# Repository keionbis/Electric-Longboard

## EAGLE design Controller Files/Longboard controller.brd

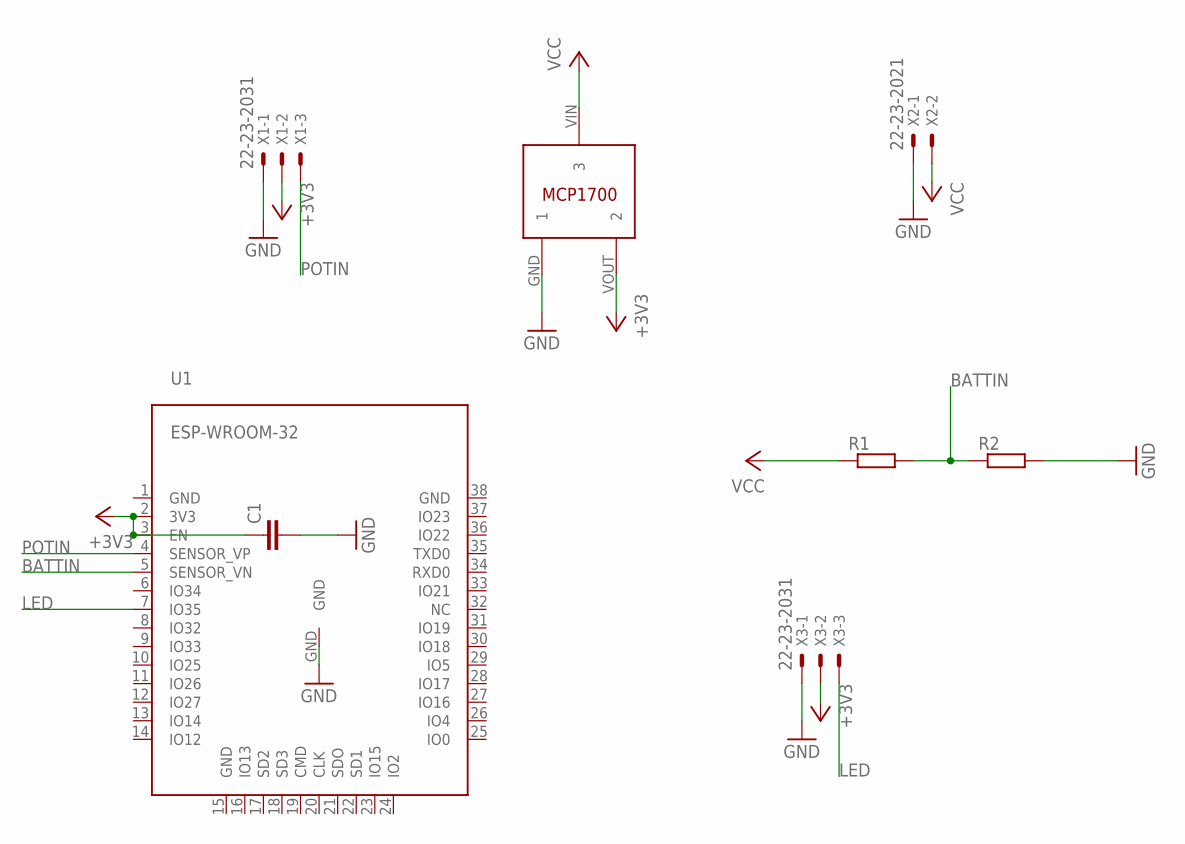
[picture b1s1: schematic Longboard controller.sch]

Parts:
C1: C-EUC0402; C0402
R1, R2: R-EU_R0805; R0805
U1: ESP-WROOM-32
U$1: MCP1700T-3302E/TT
X1, X3: 22-23-2031
X2: 22-23-2021

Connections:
+3V3: C1.1, U1.2 (3V3), U1.3 (EN), U$1.VOUT (2), X1.2, X3.2
BATTIN: R1.2, R2.1, U1.5 (SENSOR_VN)
GND: C1.2, R2.2, U1.GND, U$1.GND (1), X1.1, X2.1, X3.1
LED: U1.7 (IO35), X3.3
POTIN: U1.4 (SENSOR_VP), X1.3
VCC: R1.1, U$1.VIN (3), X2.2

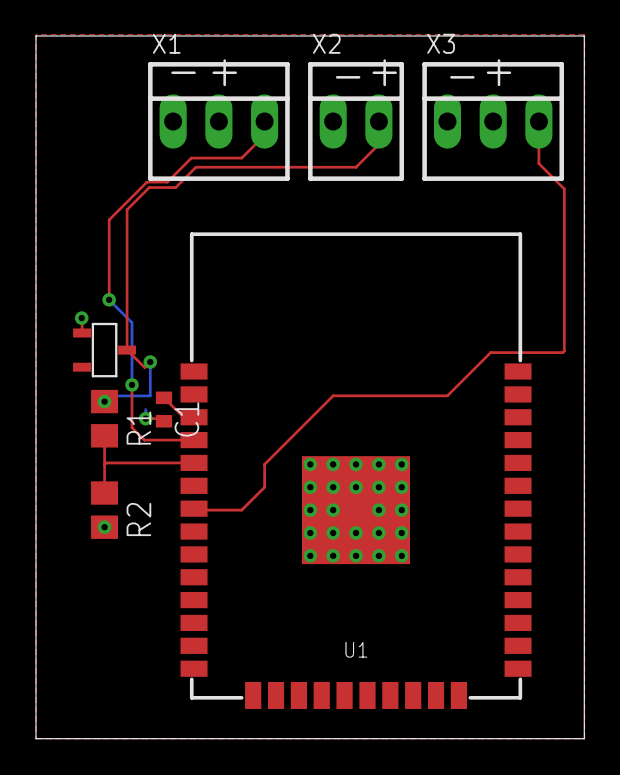
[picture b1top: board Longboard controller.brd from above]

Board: 2 copper layers, 30.5 x 39.0 mm, 8 parts (0 on the bottom side), 6 nets.

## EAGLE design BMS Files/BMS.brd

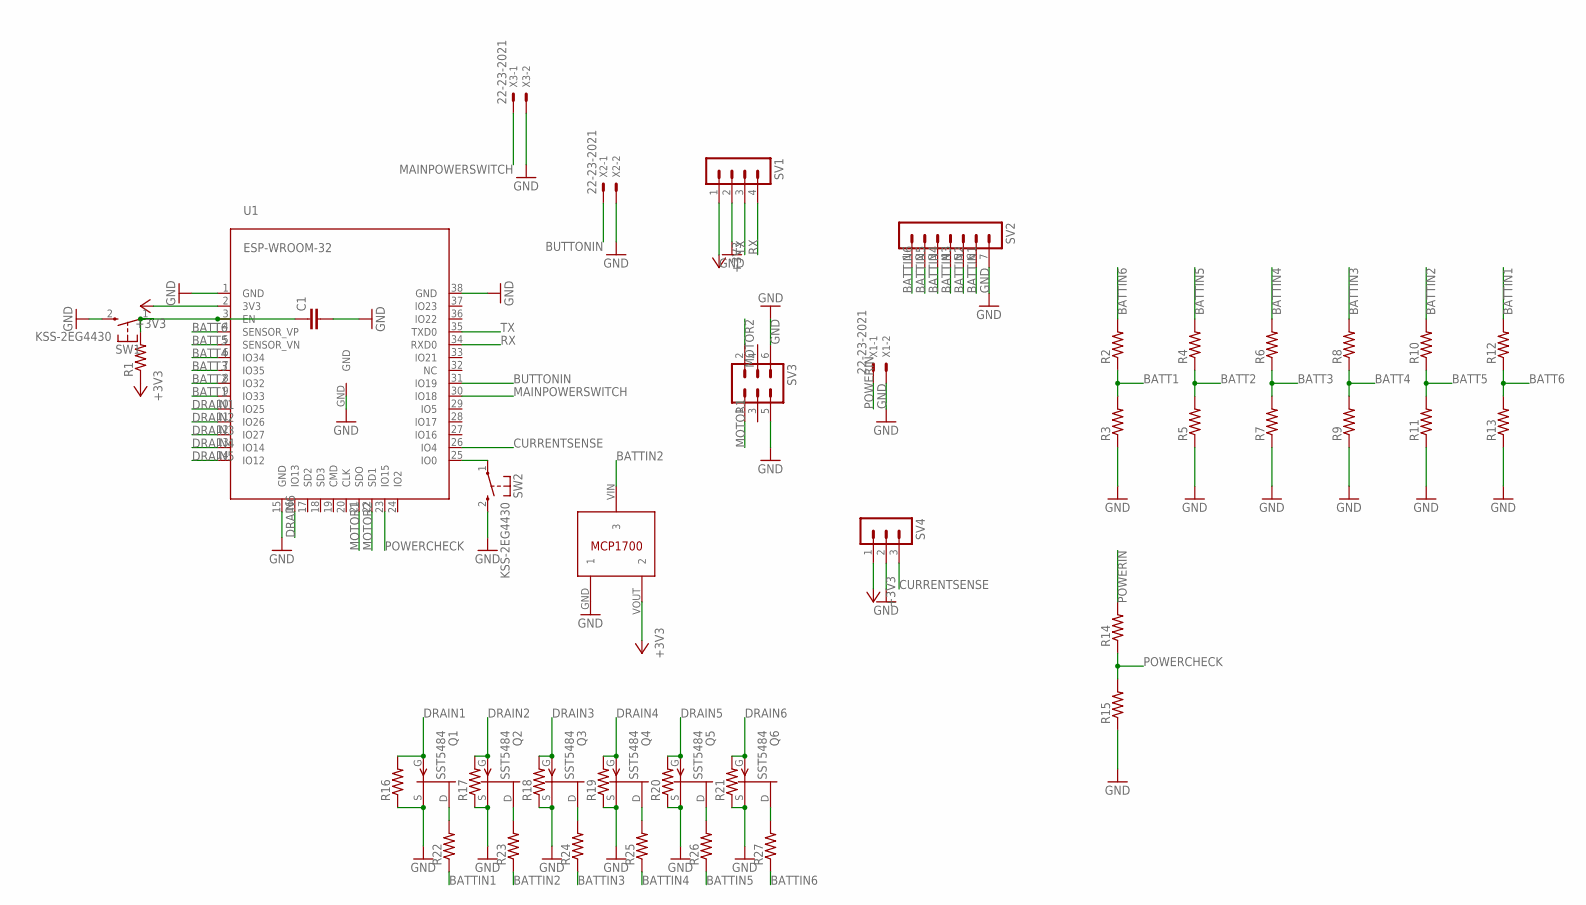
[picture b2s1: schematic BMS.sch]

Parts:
C1: C-EUC0402; C0402
Q1, Q2, Q3, Q4, Q5, Q6: SST5484; SOT23
R1: R-US_R0805; R0805
R2, R3, R4, R5, R6, R7, R8, R9, R10, R11, R12, R13, R14, R15, R16, R17, R18, R19, R20, R21, R22, R23, R24, R25, R26, R27: R-US_M0805; M0805
SV1: MA04-1
SV2: MA07-1
SV3: MA03-2
SV4: MA03-1
SW1, SW2: KSS-2EG4430
U1: ESP-WROOM-32
U$1: MCP1700T-3302E/TT
X1, X2, X3: 22-23-2021

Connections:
+3V3: R1.1, SV1.1, SV4.1, U1.2 (3V3), U$1.VOUT (2)
BATT1: R2.1, R3.2, U1.9 (IO33)
BATT2: R4.1, R5.2, U1.8 (IO32)
BATT3: R6.1, R7.2, U1.7 (IO35)
BATT4: R8.1, R9.2, U1.6 (IO34)
BATT5: R10.1, R11.2, U1.5 (SENSOR_VN)
BATT6: R12.1, R13.2, U1.4 (SENSOR_VP)
BATTIN1: R12.2, R22.1, SV2.6
BATTIN2: R10.2, R23.1, SV2.5, U$1.VIN (3)
BATTIN3: R8.2, R24.1, SV2.4
BATTIN4: R6.2, R25.1, SV2.3
BATTIN5: R4.2, R26.1, SV2.2
BATTIN6: R2.2, R27.1, SV2.1
BUTTONIN: U1.31 (IO19), X2.1
CURRENTSENSE: SV4.3, U1.26 (IO4)
DRAIN1: Q1.3 (G), R16.2, U1.10 (IO25)
DRAIN2: Q2.3 (G), R17.2, U1.11 (IO26)
DRAIN3: Q3.3 (G), R18.2, U1.12 (IO27)
DRAIN4: Q4.3 (G), R19.2, U1.13 (IO14)
DRAIN5: Q5.3 (G), R20.2, U1.14 (IO12)
DRAIN6: Q6.3 (G), R21.2, U1.16 (IO13)
GND: C1.2, Q1.2 (S), Q2.2 (S), Q3.2 (S), Q4.2 (S), Q5.2 (S), Q6.2 (S), R3.1, R5.1, R7.1, R9.1, R11.1, R13.1, R15.1, R16.1, R17.1, R18.1, R19.1, R20.1, R21.1, SV1.2, SV2.7, SV3.5, SV3.6, SV4.2, SW1.2 (S), SW2.2 (S), U1.1 (GND), U1.15 (GND), U1.38 (GND), U1.GND, U$1.GND (1), X1.2, X2.2, X3.2
MAINPOWERSWITCH: U1.30 (IO18), X3.1
MOTOR1: SV3.1, U1.21 (SDO)
MOTOR2: SV3.2, U1.22 (SD1)
unnamed: C1.1, R1.2, SW1.1, U1.3 (EN)
unnamed: SW2.1, U1.25 (IO0)
unnamed: Q6.1 (D), R27.2
unnamed: Q5.1 (D), R26.2
unnamed: Q4.1 (D), R25.2
unnamed: Q3.1 (D), R24.2
unnamed: Q2.1 (D), R23.2
unnamed: Q1.1 (D), R22.2
POWERCHECK: R14.1, R15.2, U1.23 (IO15)
POWERIN: R14.2, X1.1
RX: SV1.4, U1.34 (RXD0)
TX: SV1.3, U1.35 (TXD0)

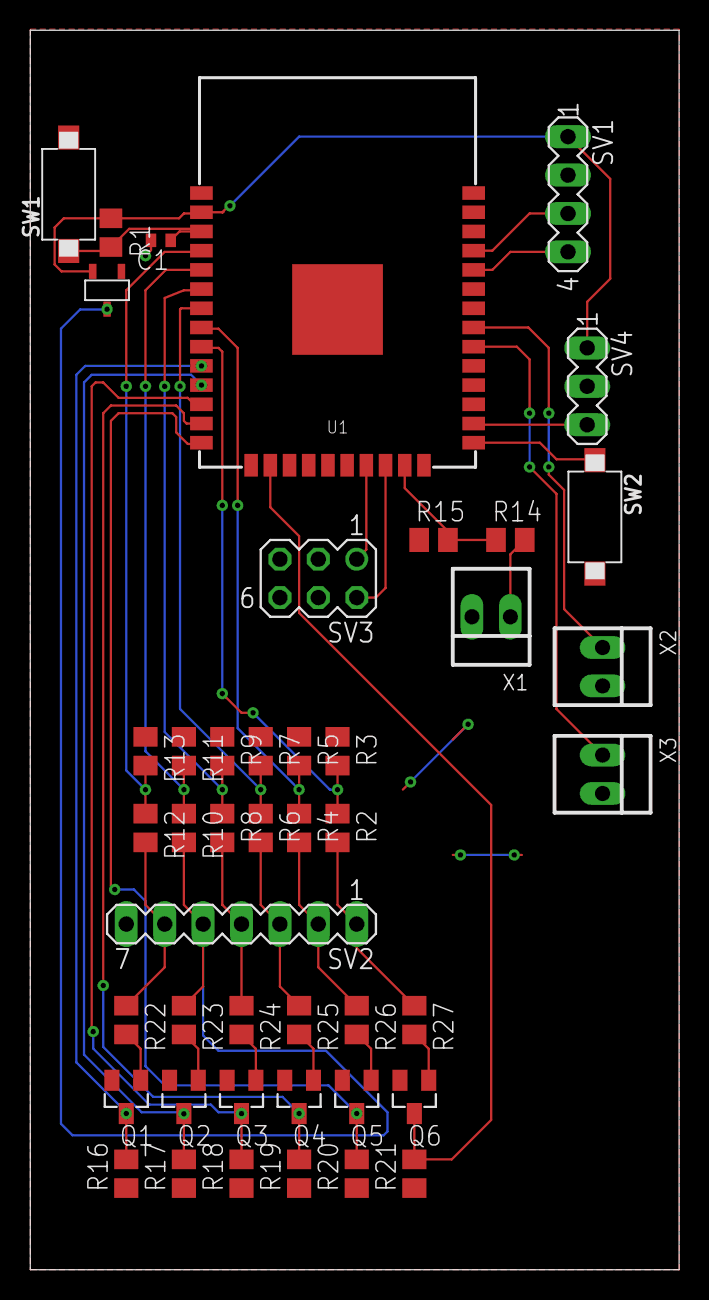
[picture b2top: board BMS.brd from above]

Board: 2 copper layers, 42.9 x 82.0 mm, 45 parts (0 on the bottom side), 37 nets.

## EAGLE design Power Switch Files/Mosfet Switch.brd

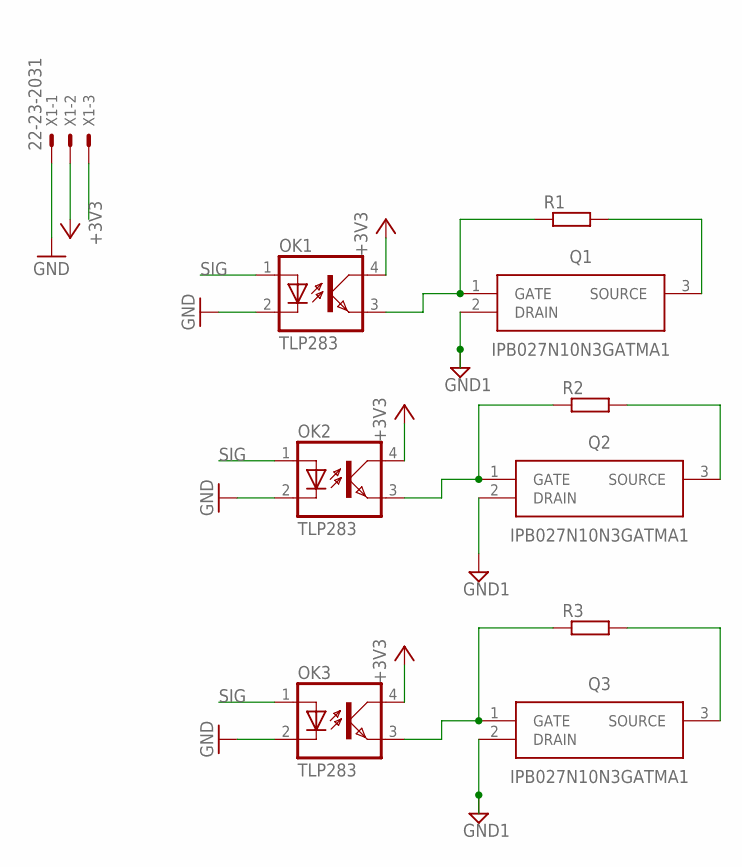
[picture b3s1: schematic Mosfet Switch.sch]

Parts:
OK1, OK2, OK3: TLP283; MINI-FLAT-4
Q1, Q2, Q3: IPB027N10N3GATMA1; PGTO263-3
R1, R2, R3: R-EU_R0805; R0805
X1: 22-23-2031

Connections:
+3V3: OK1.4 (COL), OK2.4 (COL), OK3.4 (COL), X1.2
GND1: Q1.2 (DRAIN), Q2.2 (DRAIN), Q3.2 (DRAIN)
GND2: OK1.2 (C), OK2.2 (C), OK3.2 (C), Q1.3 (SOURCE), Q2.3 (SOURCE), Q3.3 (SOURCE), R1.2, R2.2, R3.2, X1.1
unnamed: OK1.3 (EMIT), Q1.1 (GATE), R1.1
unnamed: OK2.3 (EMIT), Q2.1 (GATE), R2.1
unnamed: OK3.3 (EMIT), Q3.1 (GATE), R3.1
SIG: OK1.1 (A), OK2.1 (A), OK3.1 (A), X1.3

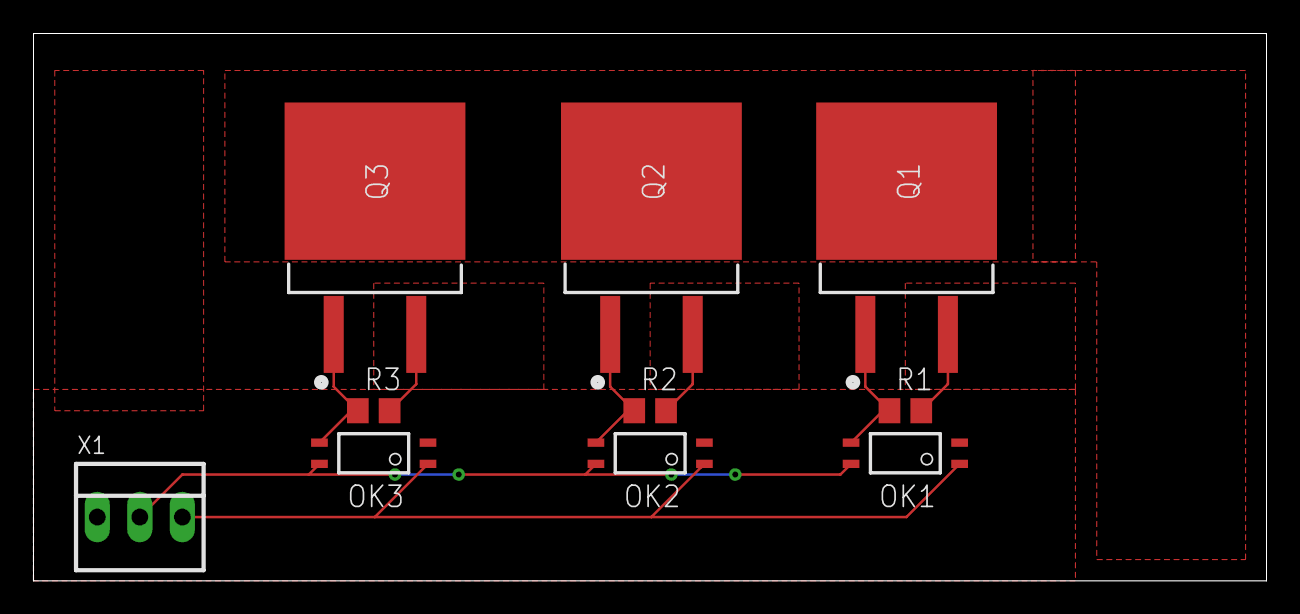
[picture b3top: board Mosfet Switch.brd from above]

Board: 2 copper layers, 73.6 x 32.7 mm, 10 parts (0 on the bottom side), 7 nets.

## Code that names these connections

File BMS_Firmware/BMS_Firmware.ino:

#include <esp_now.h>
#include <WiFi.h>
#include "esp32-hal-ledc.h"
#define CHANNEL 1
#define COUNT_LOW 0
#define COUNT_HIGH 1023
#define TIMER_WIDTH 10

#define PowerCheck 15
#define Drain1 25
#define Drain2 26
#define Drain3 27
#define Drain4 14
#define Drain5 12
#define Drain6 13
#define Batt6 36 
#define Batt5 39
#define Batt4 34
#define Batt3 35
#define Batt2 32
#define Batt1 33
#define currentSense 4

int State = 0;  //0 = driving State  1 = Charging State   2 =   

// Init ESP Now with fallback
void InitESPNow() {
  if (esp_now_init() == ESP_OK) {
    Serial.println("ESPNow Init Success");
  }
  else {
    Serial.println("ESPNow Init Failed");
    // Retry InitESPNow, add a counte and then restart?
    // InitESPNow();
    // or Simply Restart
    ESP.restart();
  }
}

// config AP SSID
void configDeviceAP() {
  char* SSID = "Slave_1";
  bool result = WiFi.softAP(SSID, "Slave_1_Password", CHANNEL, 0);
  if (!result) {
    Serial.println("AP Config failed.");
  } else {
    Serial.println("AP Config Success. Broadcasting with AP: " + String(SSID));
  }
}

void setup() {
  Serial.begin(115200);
  ledcAttachPin(32, 1);   // GPIO 22 assigned to channel 1
  ledcAttachPin(35, 2);   // GPIO 22 assigned to channel 1
  ledcSetup(7, 50, TIMER_WIDTH); // channel 1, 50 Hz, 16-bit width
  ledcSetup(8, 50, TIMER_WIDTH); // channel 1, 50 Hz, 16-bit width
  Serial.println("ESPNow/Basic/Slave Example");
  //Set device in AP mode to begin with
  WiFi.mode(WIFI_AP);
  // configure device AP mode
  configDeviceAP();
  // This is the mac address of the Slave in AP Mode
  Serial.print("AP MAC: "); Serial.println(WiFi.softAPmacAddress());
  // Init ESPNow with a fallback logic
  InitESPNow();
  // Once ESPNow is successfully Init, we will register for recv CB to
  // get recv packer info.
  esp_now_register_recv_cb(OnDataRecv);
}

// callback when data is recv from Master
void OnDataRecv(const uint8_t *mac_addr, const uint8_t *data, int data_len) {
  //if(State == 0){
  char macStr[18];
  snprintf(macStr, sizeof(macStr), "%02x:%02x:%02x:%02x:%02x:%02x",
           mac_addr[0], mac_addr[1], mac_addr[2], mac_addr[3], mac_addr[4], mac_addr[5]);
  Serial.print("Last Packet Recv from: "); Serial.println(macStr);
  Serial.print("Last Packet Recv Data: "); Serial.println(*data);
  Serial.println("");
  ledcWrite(1,map(*data,0,255,COUNT_LOW,COUNT_HIGH));
  delay(10);
  ledcWrite(2,map(*data,0,255,COUNT_LOW,COUNT_HIGH));
  delay(10);
  //}
//  else
//  {
//    //do nothing
//  }
  
}

void loop() {
//  if (analogRead(PowerCheck) >2000){
//    State = 1;
//  }
//  else
//  {
//    State = 0;
//  }
//  switch(State)
//  {
//    case(0):
//    
//      break;
//    case(1):
//      break;
//      
//  }
}

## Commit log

2017-12-03 Added Board files and start to firmware code, this is a modified version of the esp-now code, much more still to be added
2017-12-03 Began updating BMMS_Firmware
